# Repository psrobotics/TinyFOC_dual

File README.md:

# TinyFOC_dual

<br> <br>
<br> <br>

* Compact dual channel brushless motor driver with external encoder
* Inline current sensing
* 15 bit GMR-based encoder
* Hardwarer I2C, serial interface
* Input voltage: 9v - 24v, maximum phase current 1.5A
* 4 layer board / FR4 / 1.0mm thickness
* [SimpleFOC](https://github.com/simplefoc) compatible

Design file exported with [Autodesk EAGLE](https://www.autodesk.com/products/eagle/overview?term=1-YEAR&tab=subscription)

## ICs
* MCU [STM32F401CCU6](https://www.st.com/en/microcontrollers-microprocessors/stm32f401cc.html)
* Motor driver [DRV8313](https://www.ti.com/product/DRV8313?utm_source=google&utm_medium=cpc&utm_campaign=asc-null-null-GPN_EN-cpc-pf-google-wwe&utm_content=DRV8313&ds_k=DRV8313&DCM=yes&gclid=EAIaIQobChMIroSGo5PH_gIV7TatBh0lfQ1tEAAYASAAEgJeRvD_BwE&gclsrc=aw.ds) or [MS8313](https://www.lcsc.com/product-detail/Others_Hangzhou-Ruimeng-Tech-MS8313_C231942.html)
* Current sensing AMP [INA240A2PWR](https://www.ti.com/product/INA240?utm_source=google&utm_medium=cpc&utm_campaign=asc-sens-null-prodfolderdynamic-cpc-pf-google-wwe_int&utm_content=prodfolddynamic&ds_k=DYNAMIC+SEARCH+ADS&DCM=yes&gclid=EAIaIQobChMI_YzZt5PH_gIVjAKtBh2dtg4yEAAYASAAEgL9CvD_BwE&gclsrc=aw.ds)
* Encoder [TLE 5012B E1000](https://www.infineon.com/cms/en/product/sensor/magnetic-sensors/magnetic-position-sensors/angle-sensors/tle5012b-e1000/)

## Pin Out
<br> <br>

## License
MIT License

## Contact
* Shuang Peng, {shuangpe}@usc.edu

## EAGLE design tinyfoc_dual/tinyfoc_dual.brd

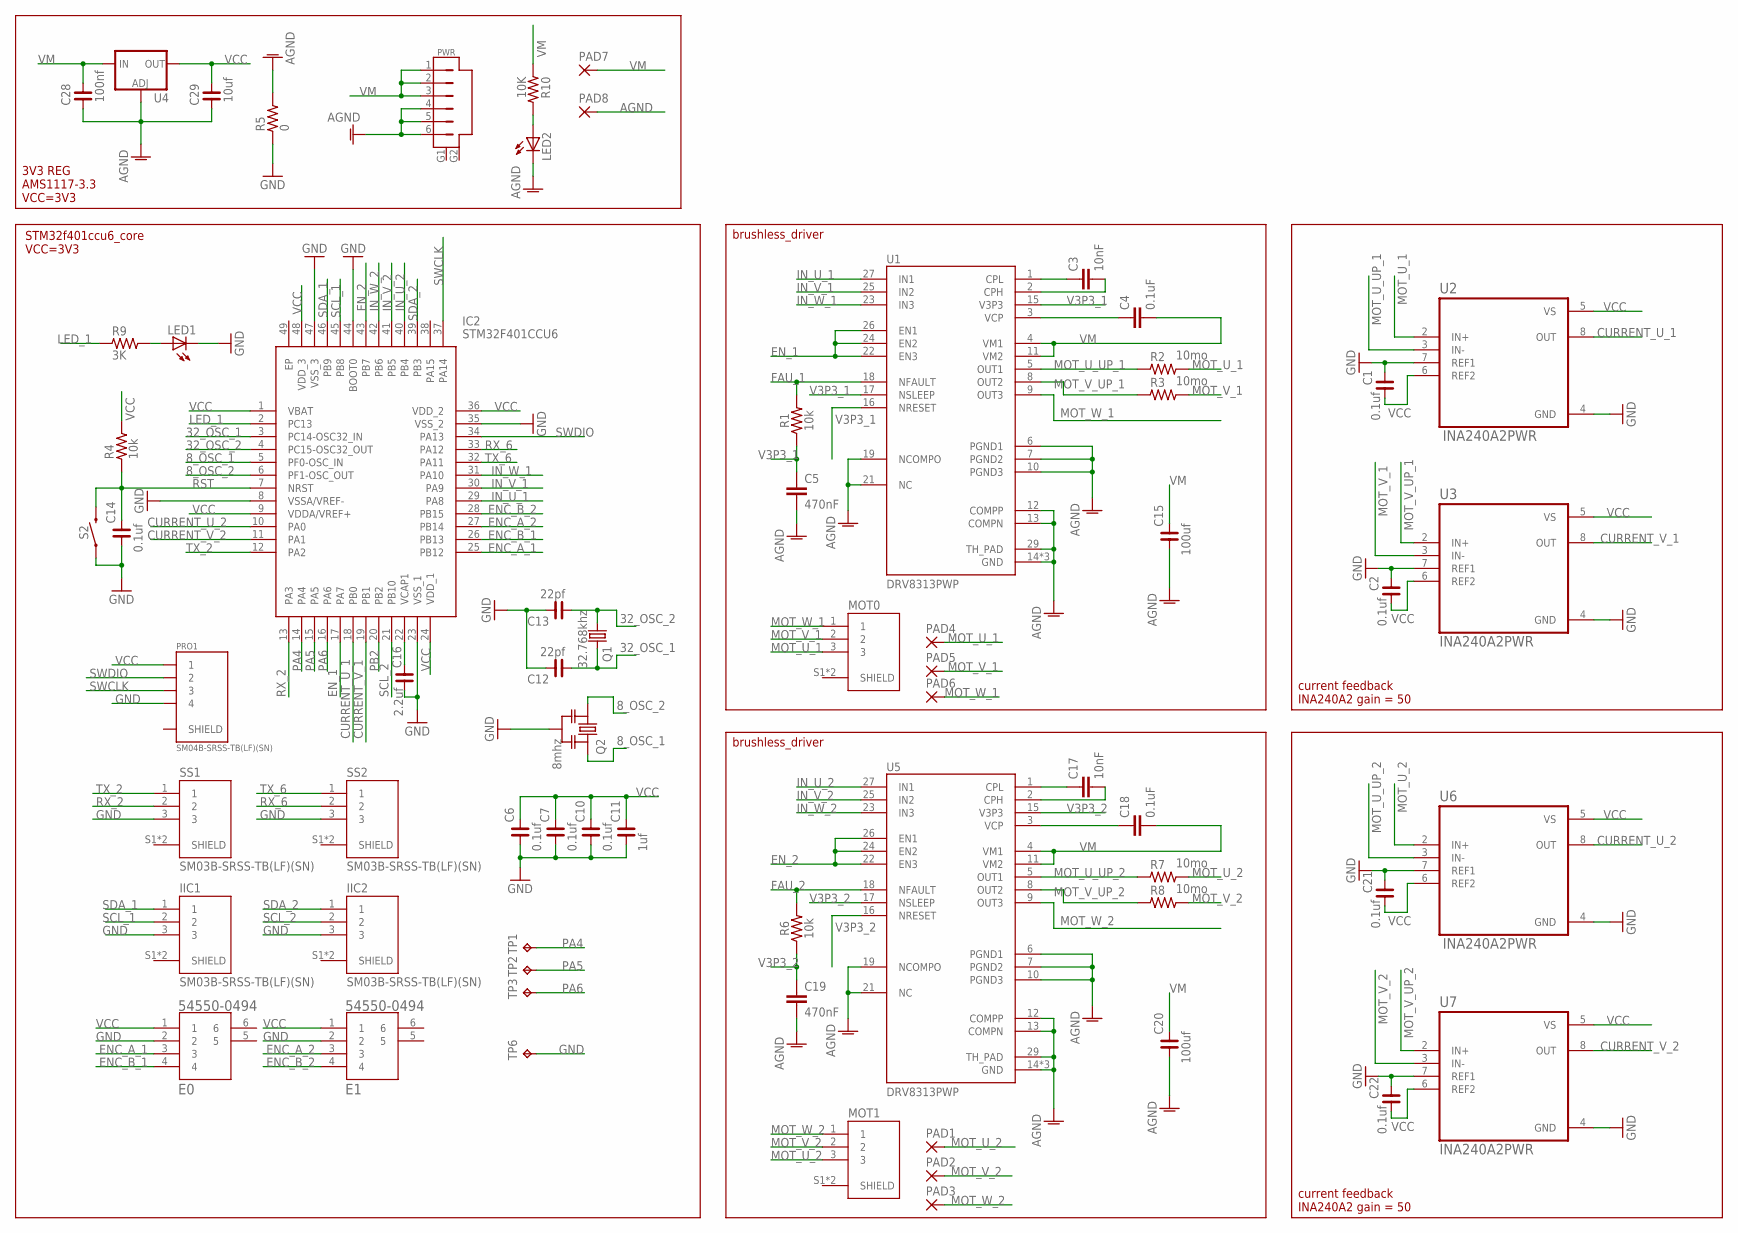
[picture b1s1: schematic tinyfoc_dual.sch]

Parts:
C1, C2, C6, C7, C10, C14, C21, C22: 0.1uf; C0603
C3, C17: 10nF; 0603
C4, C18: 0.1uF; 0603
C5, C19: 470nF; 0603
C11: 1uf; C0603
C12, C13: 22pf; C0603
C15, C20: 100uf; C1206
C16: 2.2uf; C0603
C28: 100nf; C0603
C29: 10uf; C0603
E0, E1: 54550-0494; CON4_1X4_DRB2_MOL
IC2: STM32F401CCU6; QFN50P700X700X60-49N
IIC1, IIC2: SM03B-SRSS-TB(LF)(SN); JST_SM03B-SRSS-TB(LF)(SN)
LED1, LED2: LEDCHIPLED_0603; CHIPLED_0603
MOT0, MOT1: SM03B-SRSS-TB(LF)(SN); JST_SM03B-SRSS-TB(LF)(SN)
PAD1, PAD2, PAD3, PAD4, PAD5, PAD6, PAD7, PAD8: SMD5; SMD2,54-5,08
PRO1: SM04B-SRSS-TB(LF)(SN); JST_SM04B-SRSS-TB(LF)(SN)
PWR: SM06B-SRSS-TB; SM06B
Q1: 32.768khz; 3.2X1.5
Q2: 8mhz; RESONATOR_MURATA2
R1, R6: 10k; 0603
R2, R3, R7, R8: 10mo; R1206
R4: 10k; R0603
R5: 0; R0603
R9: 3K; R0603
R10: 10K; R0603
S2: MOMENTARY-SWITCH-SPST-SMD-RIGHT-ANGLE; TACTILE_SWITCH_SMD_RIGHT_ANGLE
SS1, SS2: SM03B-SRSS-TB(LF)(SN); JST_SM03B-SRSS-TB(LF)(SN)
TP1, TP2, TP3, TP6: TPTP14SQ; TP14SQ
U1, U5: DRV8313PWP; SOP28P65_970X640X120L60X24T483X275N
U2, U3, U6, U7: INA240A2PWR; SOP65P640X120-8N
U4: V_REG_LM1117SOT223; SOT223

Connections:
8_OSC_1: IC2.5 (PF0-OSC_IN), Q2.3
8_OSC_2: IC2.6 (PF1-OSC_OUT), Q2.1
32_OSC_1: C12.1, IC2.3 (PC14-OSC32_IN), Q1.2
32_OSC_2: C13.1, IC2.4 (PC15-OSC32_OUT), Q1.1
AGND: C5.2, C15.1, C19.2, C20.1, C28.1, C29.1, LED2.C, PAD8.1, PWR.4, PWR.5, PWR.6, R5.2, U1.6 (PGND1), U1.7 (PGND2), U1.10 (PGND3), U1.12 (COMPP), U1.13 (COMPN), U1.14 (GND), U1.19 (NCOMPO), U1.20 (GND), U1.21 (NC), U1.28 (GND), U1.29 (TH_PAD), U4.1 (ADJ), U5.6 (PGND1), U5.7 (PGND2), U5.10 (PGND3), U5.12 (COMPP), U5.13 (COMPN), U5.14 (GND), U5.19 (NCOMPO), U5.20 (GND), U5.21 (NC), U5.28 (GND), U5.29 (TH_PAD)
CURRENT_U_1: IC2.18 (PB0), U2.8 (OUT)
CURRENT_U_2: IC2.10 (PA0), U6.8 (OUT)
CURRENT_V_1: IC2.19 (PB1), U3.8 (OUT)
CURRENT_V_2: IC2.11 (PA1), U7.8 (OUT)
ENC_A_1: E0.3, IC2.25 (PB12)
ENC_A_2: E1.3, IC2.27 (PB14)
ENC_B_1: E0.4, IC2.26 (PB13)
ENC_B_2: E1.4, IC2.28 (PB15)
EN_1: IC2.17 (PA7), U1.22 (EN3), U1.24 (EN2), U1.26 (EN1)
EN_2: IC2.43 (PB7), U5.22 (EN3), U5.24 (EN2), U5.26 (EN1)
FAU_1: R1.2, U1.18 (NFAULT)
FAU_2: R6.2, U5.18 (NFAULT)
GND: C1.2, C2.2, C6.1, C7.1, C10.1, C11.1, C12.2, C13.2, C14.1, C16.1, C21.2, C22.2, E0.2, E1.2, IC2.8 (VSSA/VREF-), IC2.23 (VSS_1), IC2.35 (VSS_2), IC2.44 (BOOT0), IC2.47 (VSS_3), IIC1.3, IIC2.3, LED1.C, PRO1.4, Q2.2, R5.1, S2.1, SS1.3, SS2.3, TP6.TP, U2.4 (GND), U2.7 (REF1), U3.4 (GND), U3.7 (REF1), U6.4 (GND), U6.7 (REF1), U7.4 (GND), U7.7 (REF1)
IN_U_1: IC2.29 (PA8), U1.27 (IN1)
IN_U_2: IC2.40 (PB4), U5.27 (IN1)
IN_V_1: IC2.30 (PA9), U1.25 (IN2)
IN_V_2: IC2.41 (PB5), U5.25 (IN2)
IN_W_1: IC2.31 (PA10), U1.23 (IN3)
IN_W_2: IC2.42 (PB6), U5.23 (IN3)
LED_1: IC2.2 (PC13), R9.1
MOT_U_1: MOT0.3, PAD4.1, R2.2, U2.2 (IN+)
MOT_U_2: MOT1.3, PAD1.1, R7.2, U6.2 (IN+)
MOT_U_UP_1: R2.1, U1.5 (OUT1), U2.3 (IN-)
MOT_U_UP_2: R7.1, U5.5 (OUT1), U6.3 (IN-)
MOT_V_1: MOT0.2, PAD5.1, R3.2, U3.3 (IN-)
MOT_V_2: MOT1.2, PAD2.1, R8.2, U7.3 (IN-)
MOT_V_UP_1: R3.1, U1.8 (OUT2), U3.2 (IN+)
MOT_V_UP_2: R8.1, U5.8 (OUT2), U7.2 (IN+)
MOT_W_1: MOT0.1, PAD6.1, U1.9 (OUT3)
MOT_W_2: MOT1.1, PAD3.1, U5.9 (OUT3)
unnamed: C16.2, IC2.22 (VCAP1)
unnamed: C17.1, U5.1 (CPL)
unnamed: C3.1, U1.1 (CPL)
unnamed: C3.2, U1.2 (CPH)
unnamed: C4.1, U1.3 (VCP)
unnamed: LED2.A, R10.2
unnamed: C17.2, U5.2 (CPH)
unnamed: C18.1, U5.3 (VCP)
unnamed: LED1.A, R9.2
PA4: IC2.14 (PA4), TP1.TP
PA5: IC2.15 (PA5), TP2.TP
PA6: IC2.16 (PA6), TP3.TP
PB2: IC2.20 (PB2)
RST: C14.2, IC2.7 (NRST), R4.1, S2.2
RX_2: IC2.13 (PA3), SS1.2
RX_6: IC2.33 (PA12), SS2.2
SCL_1: IC2.45 (PB8), IIC1.2
SCL_2: IC2.21 (PB10), IIC2.2
SDA_1: IC2.46 (PB9), IIC1.1
SDA_2: IC2.39 (PB3), IIC2.1
SWCLK: IC2.37 (PA14), PRO1.3
SWDIO: IC2.34 (PA13), PRO1.2
TX_2: IC2.12 (PA2), SS1.1
TX_6: IC2.32 (PA11), SS2.1
V3P3_1: C5.1, R1.1, U1.15 (V3P3), U1.16 (NRESET), U1.17 (NSLEEP)
V3P3_2: C19.1, R6.1, U5.15 (V3P3), U5.16 (NRESET), U5.17 (NSLEEP)
VCC: C1.1, C2.1, C6.2, C7.2, C10.2, C11.2, C21.1, C22.1, C29.2, E0.1, E1.1, IC2.1 (VBAT), IC2.9 (VDDA/VREF+), IC2.24 (VDD_1), IC2.36 (VDD_2), IC2.48 (VDD_3), PRO1.1, R4.2, U2.5 (VS), U2.6 (REF2), U3.5 (VS), U3.6 (REF2), U4.2 (OUT), U4.4 (OUT), U6.5 (VS), U6.6 (REF2), U7.5 (VS), U7.6 (REF2)
VM: C4.2, C15.2, C18.2, C20.2, C28.2, PAD7.1, PWR.1, PWR.2, PWR.3, R10.1, U1.4 (VM1), U1.11 (VM2), U4.3 (IN), U5.4 (VM1), U5.11 (VM2)

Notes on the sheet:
brushless_driver
current feedback INA240A2 gain = 50
STM32f401ccu6_core VCC=3V3
3V3 REG AMS1117-3.3 VCC=3V3

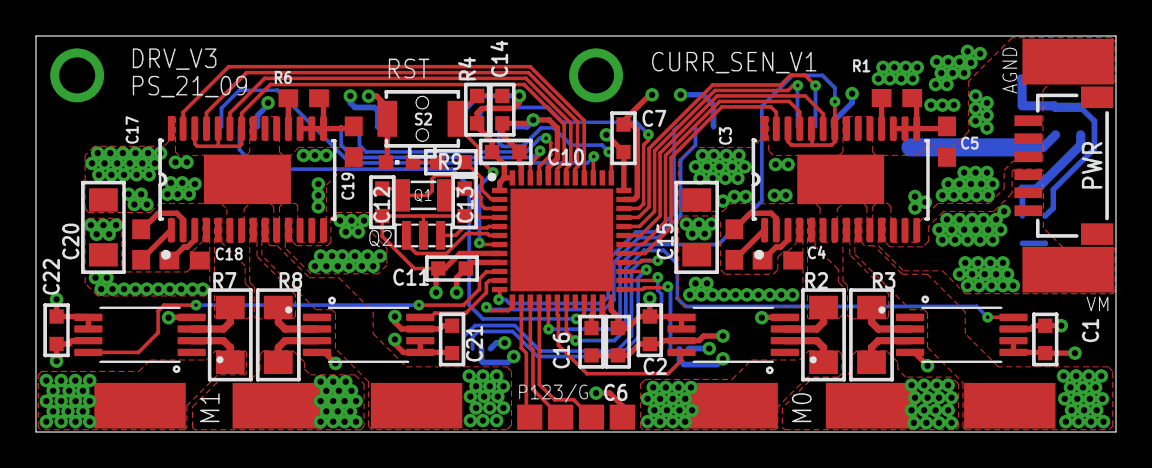
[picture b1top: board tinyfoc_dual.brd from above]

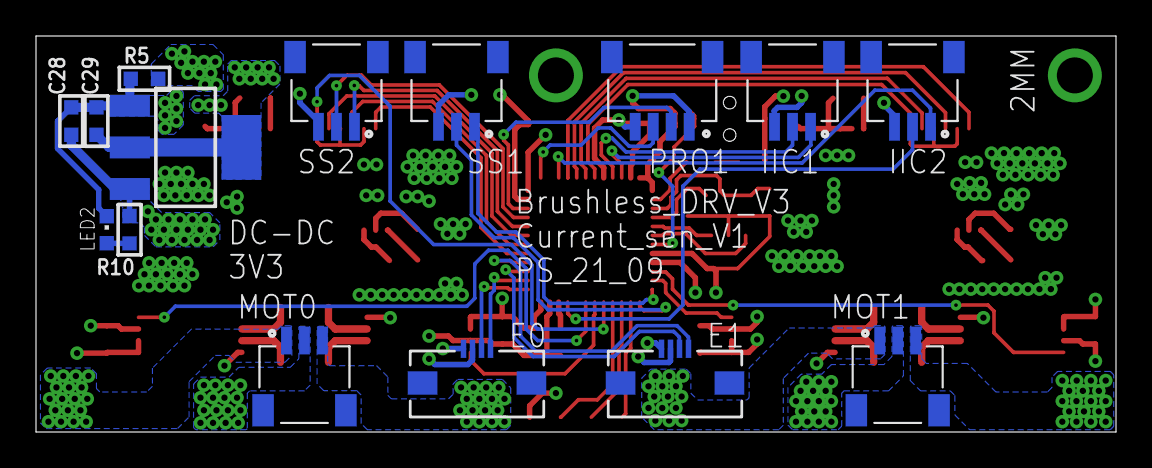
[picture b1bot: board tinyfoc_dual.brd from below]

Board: 4 copper layers, 60.0 x 22.0 mm, 67 parts (15 on the bottom side), 62 nets.

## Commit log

2023-04-26 init: 0426
2023-04-26 fix: 0426 pinout
2023-04-26 add: 0426

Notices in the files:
parts and their libraries:
rc-master-smd: Copyright (C) 2007, Bob Starr
SparkFun-Capacitors: Licensing: Creative Commons ShareAlike 4.0 International - https://creativecommons.org/licenses/by-sa/4.0
m-pad-2.1: License : GNU General Public License version 2 (see bottom)
crystal-geyer_V1_0: Copyright: Geyer-Electronic
